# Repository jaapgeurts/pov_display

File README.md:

# Rotating POV display.

These are the files to make a POV display with rotating arm.
Both the electronic schematics as well as the code is here.

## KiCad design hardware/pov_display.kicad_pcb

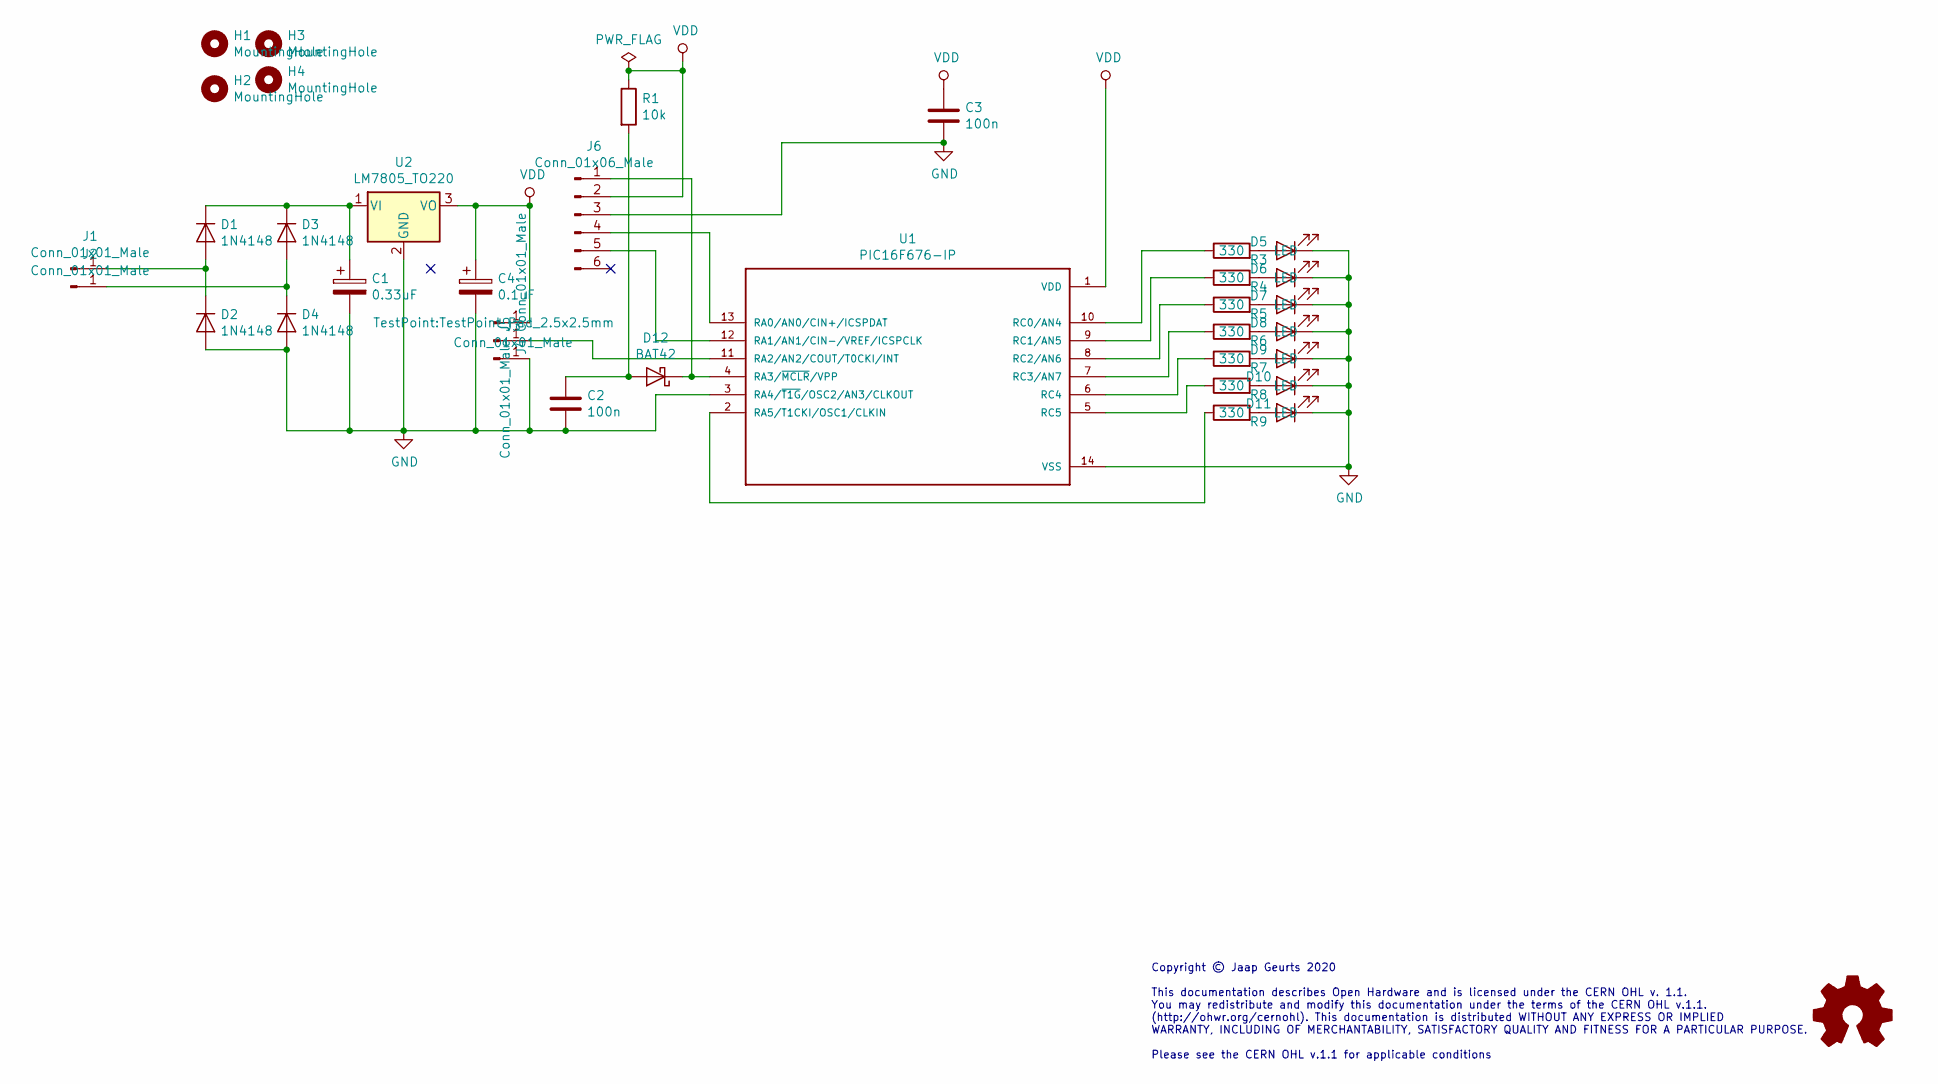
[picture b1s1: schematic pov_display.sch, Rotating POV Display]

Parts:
C1: 0.33uF; CP_Radial_D5.0mm_P2.50mm
C2: 100n; C_Disc_D5.0mm_W2.5mm_P5.00mm
C3: 100n; C_Disc_D5.0mm_W2.5mm_P2.50mm
C4: 0.1uF; CP_Radial_D5.0mm_P2.50mm
D1, D2, D3, D4: 1N4148; D_DO-35_SOD27_P7.62mm_Horizontal
D5, D6, D7, D8, D9, D10, D11: LED; LED_Rectangular_W5.0mm_H5.0mm
D12: BAT42; D_DO-35_SOD27_P7.62mm_Horizontal
H1, H2, H3, H4: MountingHole; MountingHole_3.2mm_M3
J1, J2, J3, J4, J5: Conn_01x01_Male; TestPoint_Pad_2.5x2.5mm
J6: Conn_01x06_Male; PinHeader_1x06_P2.54mm_Vertical
R1: 10k; R_Axial_DIN0207_L6.3mm_D2.5mm_P10.16mm_Horizontal
R3, R4, R5, R6, R7, R8, R9: 330; R_Axial_DIN0207_L6.3mm_D2.5mm_P10.16mm_Horizontal
U1: PIC16F676-IP; DIP-14_W7.62mm_Socket_LongPads
U2: LM7805_TO220; TO-220-3_Vertical

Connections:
GND: C1.2, C2.2, C3.2, C4.2, D2.2 (A), D4.2 (A), D5.1 (K), D6.1 (K), D7.1 (K), D8.1 (K), D9.1 (K), D10.1 (K), D11.1 (K), J3.1, J6.3, U1.3 (RA4/~T1G~/OSC2/AN3/CLKOUT), U1.14 (VSS), U2.2 (GND)
unnamed: C1.1, D1.1 (K), D3.1 (K), U2.1 (VI)
unnamed: C2.1, D12.2 (A), R1.2
unnamed: D1.2 (A), D2.1 (K), J1.1
unnamed: D3.2 (A), D4.1 (K), J2.1
unnamed: D5.2 (A), R3.2
unnamed: D6.2 (A), R4.2
unnamed: D7.2 (A), R5.2
unnamed: D8.2 (A), R6.2
unnamed: D9.2 (A), R7.2
unnamed: D10.2 (A), R8.2
unnamed: D11.2 (A), R9.2
unnamed: D12.1 (K), J6.1, U1.4 (RA3/~MCLR~/VPP)
unnamed: J5.1, U1.11 (RA2/AN2/COUT/T0CKI/INT)
unnamed: J6.4, U1.13 (RA0/AN0/CIN+/ICSPDAT)
unnamed: J6.5, U1.12 (RA1/AN1/CIN-/VREF/ICSPCLK)
unnamed: R3.1, U1.10 (RC0/AN4)
unnamed: R4.1, U1.9 (RC1/AN5)
unnamed: R5.1, U1.8 (RC2/AN6)
unnamed: R6.1, U1.7 (RC3/AN7)
unnamed: R7.1, U1.6 (RC4)
unnamed: R8.1, U1.5 (RC5)
unnamed: R9.1, U1.2 (RA5/T1CKI/OSC1/CLKIN)
VDD: C3.1, C4.1, J4.1, J6.2, R1.1, U1.1 (VDD), U2.3 (VO)

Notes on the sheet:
Copyright © Jaap Geurts 2020 This documentation describes Open Hardware and is licensed under the CERN OHL v. 1.1. You may redistribute and modify this documentation under the terms of the CERN OHL v.1.1. (http://ohwr.org/cernohl). This documentation is distributed WITHOUT ANY EXPRESS OR IMPLIED WA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

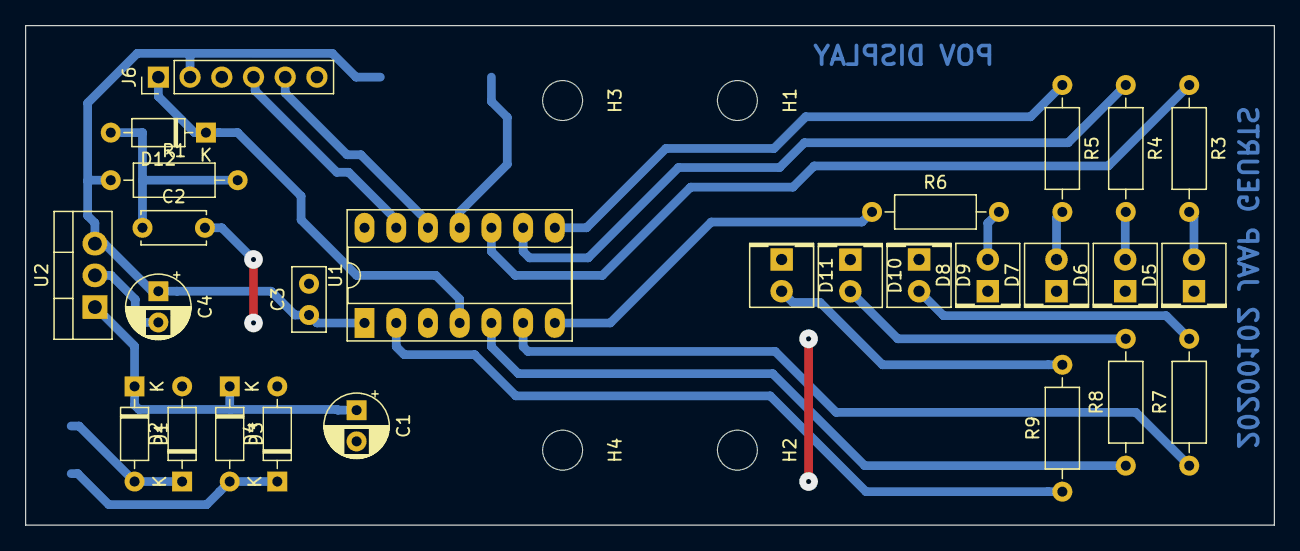
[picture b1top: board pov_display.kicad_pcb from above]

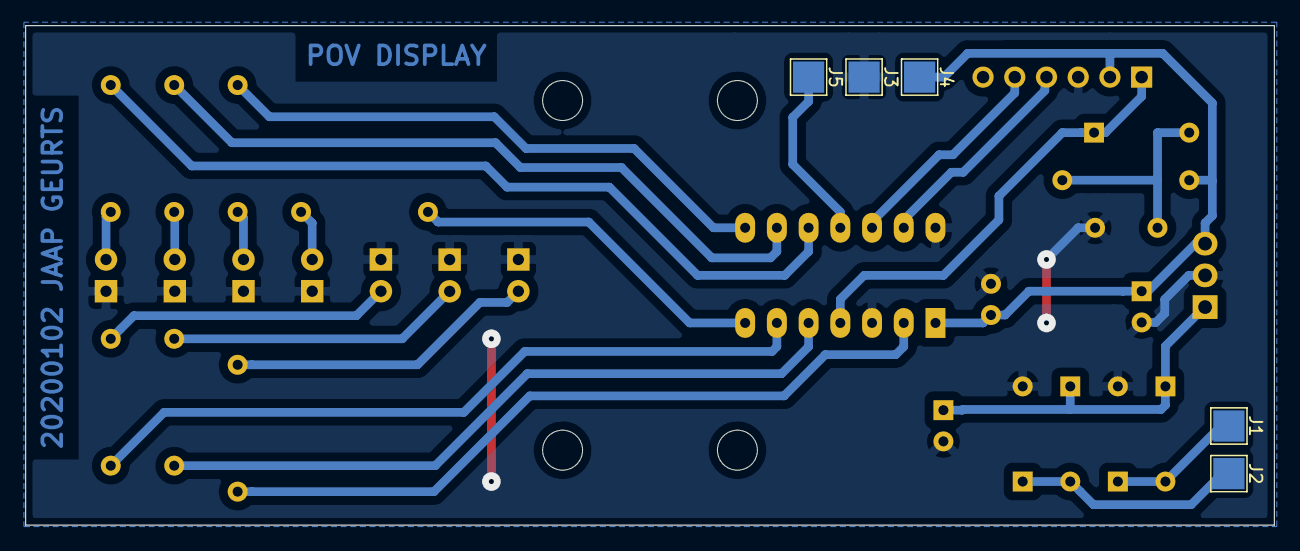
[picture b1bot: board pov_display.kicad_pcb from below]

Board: 2 copper layers, 100.0 x 40.0 mm, 36 parts (5 on the bottom side), 24 nets.

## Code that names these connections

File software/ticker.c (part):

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

// CONFIG
//#pragma config FOSC = INTRCIO  // Oscillator Selection bits (INTOSC oscillator: CLKOUT function on RA4/OSC2/CLKOUT pin, I/O function on RA5/OSC1/CLKIN)
//#pragma config WDTE = OFF       // Watchdog Timer Enable bit (WDT disabled)
//#pragma config PWRTE = OFF      // Power-up Timer Enable bit (PWRT disabled)
//#pragma config MCLRE = ON       // RA3/MCLR pin function select (RA3/MCLR pin function is MCLR)
//#pragma config BOREN = OFF      // Brown-out Detect Enable bit (BOD disabled)
//#pragma config CP = OFF         // Code Protection bit (Program Memory code protection is disabled)
//#pragma config CPD = OFF        // Data Code Protection bit (Data memory code protection is disabled)
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  else {
    // show nothing
    PORTC = 0x00;
    RA5 = 0;
  }

}
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  else {
    // show nothing
    PORTC = 0x00;
    RA5 = 0;
  }
}

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  // set data direction
  TRISA = 0x05; // portA as output, except RA0,RA2
  //  TRISA = 0x00; // portA as output
  //  TRISA0 = 1; // except RA0
  //  TRISA2 = 1; // except RA2
  TRISC = 0x00; // portC as output


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
  INTF = 0; // clear INT flag
  INTEDG = 0; //  trigger on rising edge
  INTE = 1; // enable external interrupt on RA2
  GIE = 1; // enable global interrupts

  forever{
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
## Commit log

2020-01-05 Initial commit. First test. Not enough memory
2020-01-06 Timing is off, but dots showing independent of RPM
2020-01-07 Seemingly working version
2020-01-08 Added letter to c array converter. Now shows rotating short text!!!
2020-01-08 Bug fix
2020-01-09 Added 5x7 fonts. Font converter v2. Minor bug when text passes 0 point
2020-01-11 ALmost working version
2020-01-15 Added message to code generator
2020-01-18 Working version with short message
2020-01-19 Long banners now supported in both ticker and drytest
2020-03-11 Updated to latest code version
2020-03-11 Added hardware and reorganized project
2020-03-11 Cosmetic updates, removed unwanted files
2020-03-11 Added license files
